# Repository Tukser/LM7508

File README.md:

# LM7508 voltage regulators 
## Регулятор напряжения LM7508 5v

Принципиальная электрическая схема

Трассировка печатной платы

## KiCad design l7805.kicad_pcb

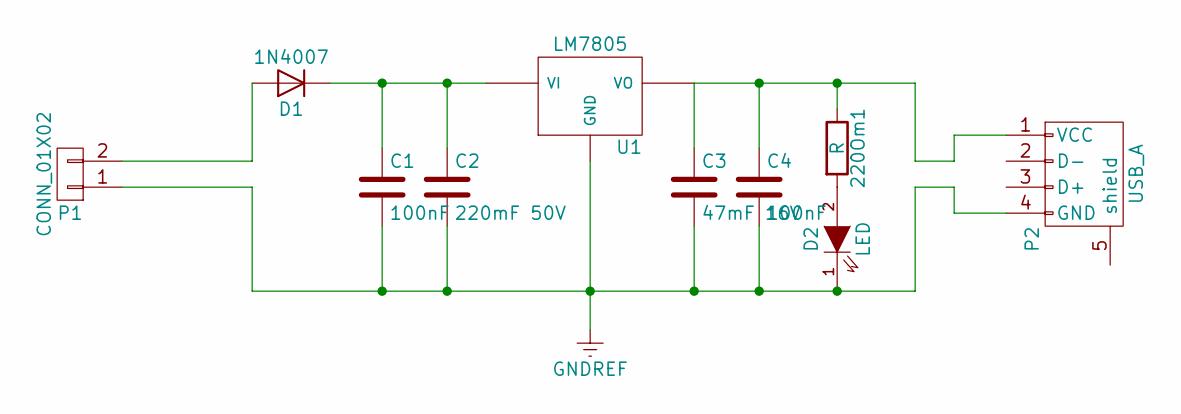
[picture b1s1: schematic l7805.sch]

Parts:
220Om1: R; R_1206
C1, C4: 100nF; C_1206
C2: 220mF 50V; C_Radial_D6.3_L11.2_P2.5
C3: 47mF 16V; C_Radial_D6.3_L11.2_P2.5
D1: 1N4007; Diode_DO-41_SOD81_Horizontal_RM10
D2: LED; LED-3MM
P1: CONN_01X02; Pin_Header_Angled_1x02
P2: USB_A
U1: LM7805; TO-220_Neutral123_Horizontal

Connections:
GNDREF: C1.2, C2.2, C3.2, C4.2, D2.1 (K), P1.1, P2.4 (GND), U1.GND
unnamed: 220Om1.1, C3.1, C4.1, P2.1 (VCC), U1.VO
unnamed: 220Om1.2, D2.2 (A)
unnamed: C1.1, C2.1, D1.1 (K), U1.VI
unnamed: D1.2 (A), P1.2

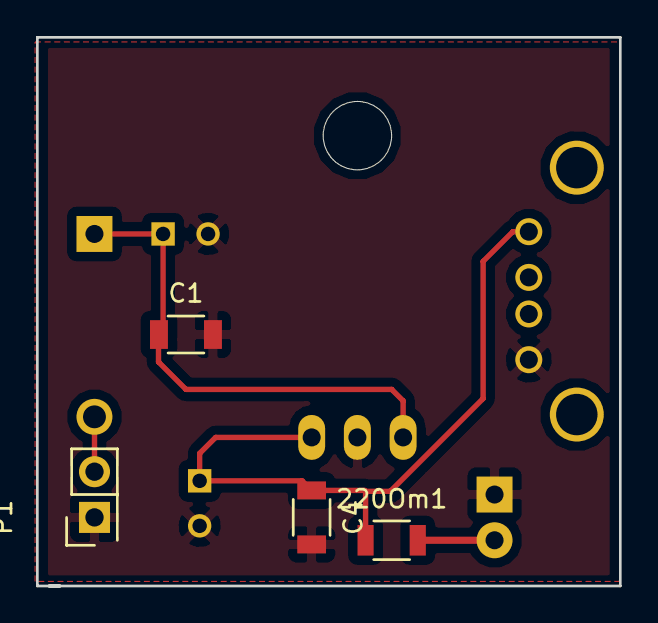
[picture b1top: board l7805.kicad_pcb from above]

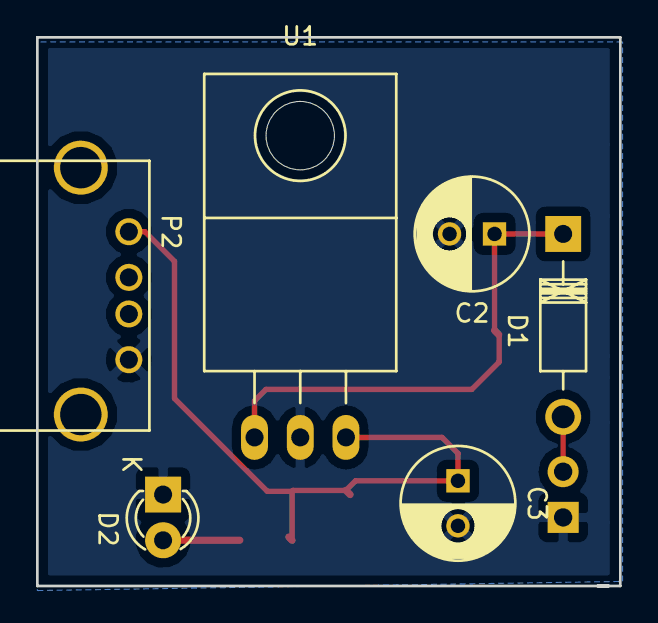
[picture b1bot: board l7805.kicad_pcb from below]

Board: 2 copper layers, 32.4 x 30.5 mm, 10 parts (6 on the bottom side), 5 nets.
